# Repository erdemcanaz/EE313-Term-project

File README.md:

<h1 align="center" style=" border-bottom: none ;">Implementing An Analog Approach For Closed Environment Autonomous Temperature Control Circuitry </h1>
<h3 align="center" style="font-style: italic;font-size:2em;">  EE-313 TERM PROJECT </h3>

<h3 align="center" style="font-style: italic;font-size:2em;">  General requirements </h3>

<p>The project consists of five units; namely, <b>sensing, set, control, operation and display units</b>. The sensing unit perceives the ambient temperature and sends this information to the control and display units. Similarly, set unit receives an input from the user indicating the desired temperature level and send this information to control and display units. Control unit compares the two temperatures and decides the action to be taken by the operation unit. Operation unit is where the heating and cooling systems are present. It perates one of these systems according to the signal sent from the control unit. Display unit shows the ambient and set temperatures by mapping them into a color spectrum</p>

<p align="center" width="100%">   
    <b> </b>
</p>

<h3 align="center" style="font-style: italic;font-size:2em;"> Sensing Unit </h3>

<p> Sensing unit output voltage (Vsensing) is 0V and 9V voltage for the 24◦C and 40◦C temperatures, respectively. Between these temperature levels, it has a linear increase in the output voltage. Outside of this temperature range, it performs clipping in the voltage levels. The temperature sensor used (LM35) has lienar characteristics and outputs 240mV and 400mv for 24◦C and 40◦C temperatures respectively. By subtracting 240mV and multiplying the result with 56 (160 mV x 56=8.96V), we can get desired output characteristics. Yet another problem to solve is to constrain this voltage in between 0-9Volts. Which can be done by a diode an a 9.1V zenner diode.
   <ol>
   <li><b> Voltage Reference Stage:</b> At this stage, about 240mV+(0.7)/56 is generated. 240mV is due to LM35 and (0.7)/56 is due to forward voltage drop of diode D1. Even though R3 & R4 is >> R1,R2 % R_POT; this voltage reference is not isolated. Also forward votlage drop of the diode may not be exactly 0.7Volts. Thus, a potentiometer is used to find exact point where output is 0 volt at 24C and starts to increase just after that. Then, potentiometer is replaced by resistors. </li>
   <li><b> Subtraction and Amplification Stage:</b> At this stage, reference voltage is subtracted froum LM35 voltage output. The result is multiplied by the ratio of R4/R3. We chosed R4/R3 as 56.</li>
   <li><b> Clipping Stage:</b> This stage rectifies the output of the subtraction stage due to <b>D1</b>. And if voltage of the previous stage is greater than <b>V_Z2</b>, <b> Z2</b> is activated and voltage upper limit is set.</li>
   <li><b> Buffering Stage:</b> This stage buffers the output.</li>
   </ol> 
   Experimentally measured input output characteristics and stability of the reference stage due to unstable buss voltage are given below.   
</p> 

<h3 align="center" style="font-style: italic;font-size:2em;"> Set Unit </h3>
Desired temperature is set by adjusting the the potentiometer's knob. The schematic is self explanatory. <b> R1, R2 and R_POT</b> ensures voltage of the second leg of the potentiometer is greater than 0.25V and less than 8.75V. 

<b> </b>

<h3 align="center" style="font-style: italic;font-size:2em;"> Control Unit </h3>

<h3 align="center" style="font-style: italic;font-size:2em;"> Operation Unit: Heating and Cooling </h3>
<h3 align="center" style="font-style: italic;font-size:2em;"> Display Unit </h3>

<h1 align="center" style=" border-bottom: none ;">THANKS! </h1>

<p align="center" width="100%">   
   <b>Semanur Avşar</b> (Left) & <b>Erdem Canaz</b>  (right) <br>   https://youtu.be/WysXOD-1qQ8
</p>

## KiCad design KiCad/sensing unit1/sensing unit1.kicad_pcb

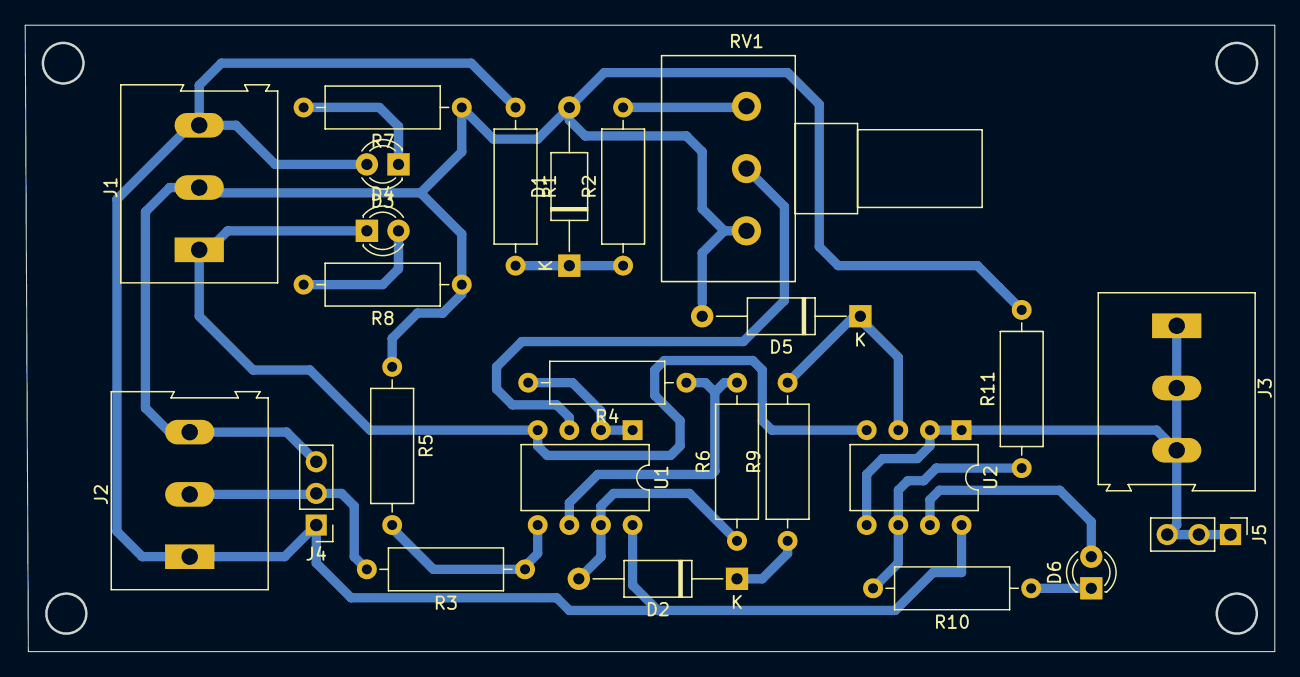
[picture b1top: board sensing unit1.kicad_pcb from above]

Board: 2 copper layers, 100.2 x 50.1 mm, 25 parts (0 on the bottom side), 19 nets.

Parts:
D1: 5.1V; D_A-405_P12.70mm_Horizontal
D2: D; D_A-405_P12.70mm_Horizontal
D3: GREEN; LED_D3.0mm_FlatTop
D4: BLUE; LED_D3.0mm_FlatTop
D5: 4.7V; D_A-405_P12.70mm_Horizontal
D6: RED; LED_D3.0mm_FlatTop
J1, J2, J3: Conn_01x03_Male; TerminalBlock_Altech_AK300-3_P5.00mm
J4, J5: Conn_01x03_Male; PinHeader_1x03_P2.54mm_Vertical
R1: 3k; R_Axial_DIN0309_L9.0mm_D3.2mm_P12.70mm_Horizontal
R2: 50k; R_Axial_DIN0309_L9.0mm_D3.2mm_P12.70mm_Horizontal
R3, R4, R10: 1k; R_Axial_DIN0309_L9.0mm_D3.2mm_P12.70mm_Horizontal
R5, R6: 25k; R_Axial_DIN0309_L9.0mm_D3.2mm_P12.70mm_Horizontal
R7, R8: 1.2k; R_Axial_DIN0309_L9.0mm_D3.2mm_P12.70mm_Horizontal
R9: 10k; R_Axial_DIN0309_L9.0mm_D3.2mm_P12.70mm_Horizontal
R11: 330; R_Axial_DIN0309_L9.0mm_D3.2mm_P12.70mm_Horizontal
RV1: 5k; Potentiometer_Alps_RK163_Single_Horizontal
U1, U2: LM358; DIP-8_W7.62mm

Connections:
12V: D3.2, J1.3, J2.1, J4.1, R1.1, U1.8, U2.8
-12V: D4.1, J1.1, U1.4, U2.4
GND: D1.2, D5.2, J1.2, J2.3, J4.3, R5.1, R7.1, R8.1, R11.2, RV1.1
LM35: J2.2, J4.2, R3.2
unnamed: D1.1, R1.2, R2.1
unnamed: D2.1, R9.1
unnamed: D2.2, R6.1, U1.7
unnamed: D3.1, R7.2
unnamed: D4.2, R8.2
unnamed: D5.1, R9.2, U2.3
unnamed: D6.1, R10.1
unnamed: D6.2, U2.7
unnamed: R2.2, RV1.3
unnamed: R3.1, R5.2, U1.5
unnamed: R4.1, R6.2, U1.6
unnamed: R4.2, U1.1, U1.2
unnamed: R10.2, R11.1, U2.6
unnamed: RV1.2, U1.3
Vout: J3.1, J3.2, J3.3, J5.1, J5.2, J5.3, U2.1, U2.2, U2.5

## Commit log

2022-01-02 Temperature mapping
    [24C-40C] temperature range is mapped to [0,4.7V]
2022-01-02 Sensing unit
    .
2022-01-02 .
    .
2022-01-02 Display-blue finished
    .
2022-01-02 Display is finished
    .
2022-01-02 Control Unit
    .
2022-01-15 PCB design for sensing unit
    .
2022-01-15 Sensing unit PCB
    .
2022-01-15 Schmith trigger
    .
2022-01-28 Control unit simulation is finished (4)
    I used schmidt trigger to guarantee the stable control output.
2022-01-28 display unit is finished
    .
2022-01-28 cotrol unit4- schematic is finished
    .
2022-01-28 PCB of Control unit 4 is finished
    .
2022-01-28 display unit3 simulation
    .
2022-01-28 display unit 3- schematic is finished
    .
2022-01-28 display unit 3 PCB is finished
    .
2022-02-09 Final report is finished
    .
